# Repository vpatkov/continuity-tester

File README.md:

# Continuity Tester

Ultra low-voltage and fast continuity tester. Digital multimeters are very good
at precise measurements but usually not so good at continuity testing. This
little tester solves the problem.

- **Open terminals voltage is 100 mV, short terminals current is 100 μA.**
  Suitable for in-circuit testing (keep p-n junctions closed) without the
  risk of damaging sensitive components. DMMs usually apply several volts or
  milliamps to the terminals (and not always specified).

- **Resistance-dependent beeper tones with chromatic steps.**
  Allows you to differentiate resistance by ear without moving your viewpoint.
  The range is 0–10 Ω with 1 Ω steps. DMMs usually have a pretty big threshold
  and require you to look at the screen to read the resistance, e.g. if you
  want to catch a bad connection.

- **Detects shorts of 1 ms with an ensured minimal beep duration of 100 ms.**
  Suitable for finding connections by sweeping and brushing without the risk
  of missing a beep. Gold-plated probes are recommended.

- **Auto-hold the minimal resistance.**
  Helps against unstable contacts, e.g. on dirty, oxidized, or lacquered
  boards. The hold resets when the resistance becomes greater than 10 Ω.

- **200 working hours on a single CR2032 cell.**
  Consumes 0.7 mA when on (+0.3 mA when beeping), 0.1 μA when off. After 3
  minutes of inactivity the tester switched off automatically.

- **±30 V input protection.**
  The tester should not be used on a powered circuit, but just in case.
  Also saves against charged capacitors. The input impedance of the tester is
  1 kΩ, so the risk of damaging an accidentally powered circuit under test is
  also low.

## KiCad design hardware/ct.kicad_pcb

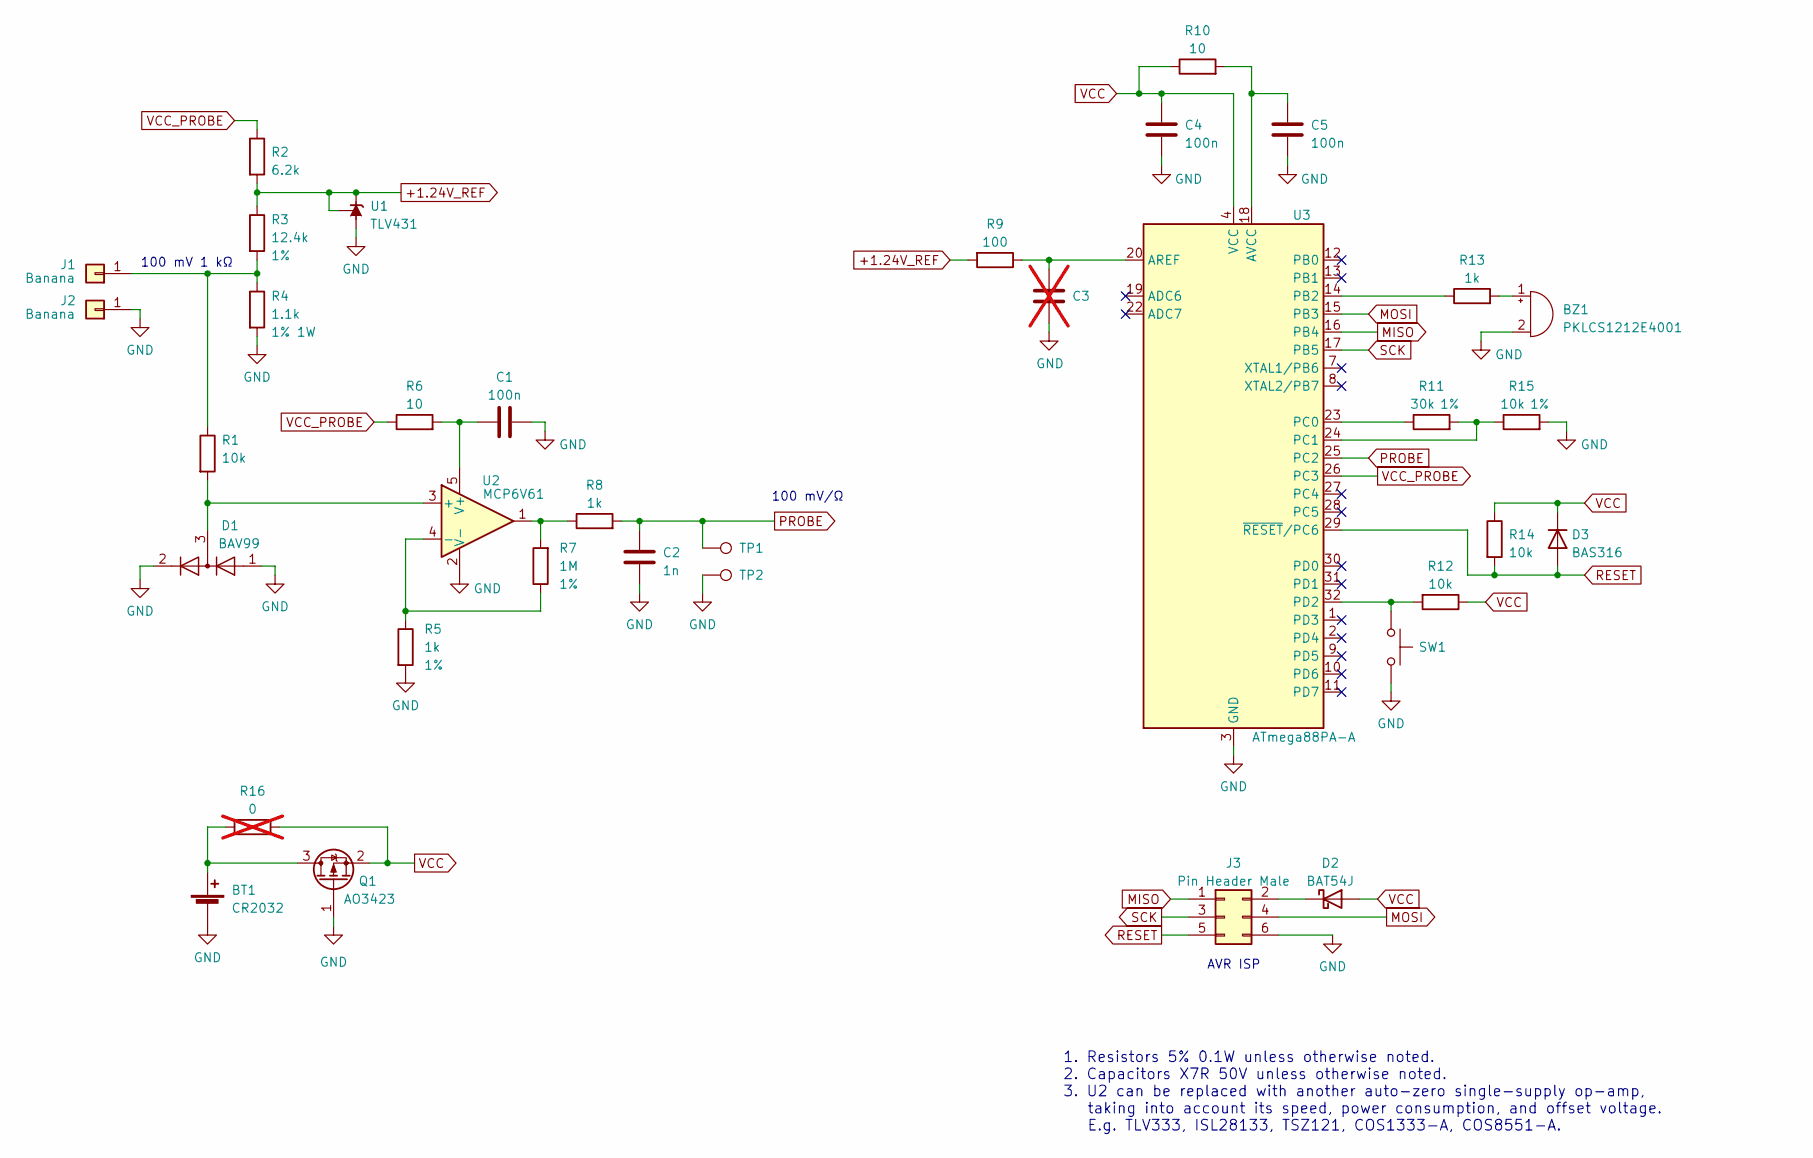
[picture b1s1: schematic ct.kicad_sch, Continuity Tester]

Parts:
BT1: CR2032; BatteryHolder_MPD_BC2003_1x2032
BZ1: PKLCS1212E4001; Buzzer_Murata_PKLCS1212E
C1, C4, C5: 100n; C_0603_1608Metric
C2: 1n; C_0603_1608Metric
C3: C_0603_1608Metric; not fitted
D1: BAV99; SOT-23
D2: BAT54J; D_SOD-323F
D3: BAS316; D_SOD-323
J1, J2: Banana; Banana_Cliff_FCR7350x_S16N-PC_Horizontal
J3: Pin Header Male; PinHeader_2x03_P2.54mm_Vertical
Q1: AO3423; SOT-23
R1, R12, R14, R15: 10k; R_0603_1608Metric
R2: 6.2k; R_0603_1608Metric
R3: 12.4k; R_0603_1608Metric
R4: 1.1k; R_2512_6332Metric
R5, R8, R13: 1k; R_0603_1608Metric
R6, R10: 10; R_0603_1608Metric
R7: 1M; R_0603_1608Metric
R9: 100; R_0603_1608Metric
R11: 30k; R_0603_1608Metric
R16: 0; R_0603_1608Metric; not fitted
SW1: Tactile Button; SW_PUSH_6mm
TP1, TP2: TestPoint; TestPoint_Loop_D3.50mm_Drill0.9mm_Beaded
U1: TLV431; SOT-23
U2: MCP6V61; SOT-23-5
U3: ATmega88PA-A; TQFP-32_7x7mm_P0.8mm

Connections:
+1.24V_REF: R2.2, R3.1, R9.2, U1.1 (K), U1.2 (REF)
GND: BT1.2 (-), BZ1.2 (+), C1.2, C2.2, C3.2, C4.2, C5.2, D1.1 (K), D1.2 (A), J2.1, J3.6, Q1.1 (G), R4.2, R5.2, R15.2, SW1.2, TP2.1, U1.3 (A), U2.2 (V-), U3.3 (GND), U3.5 (GND), U3.21 (GND)
MISO: J3.1, U3.16 (PB4)
MOSI: J3.4, U3.15 (PB3)
unnamed: BT1.1 (+), Q1.3 (D), R16.1
unnamed: BZ1.1 (-), R13.2
unnamed: D2.1 (K), J3.2
unnamed: J1.1, R1.1, R3.2, R4.1
unnamed: R7.2, R8.1, U2.1
unnamed: D1.3 (K), R1.2, U2.3 (+)
unnamed: R5.1, R7.1, U2.4 (-)
unnamed: C1.1, R6.2, U2.5 (V+)
unnamed: C3.1, R9.1, U3.20 (AREF)
unnamed: C5.1, R10.2, U3.18 (AVCC)
unnamed: R13.1, U3.14 (PB2)
unnamed: R11.1, U3.23 (PC0)
unnamed: R11.2, R15.1, U3.24 (PC1)
unnamed: R12.2, SW1.1, U3.32 (PD2)
PROBE: C2.1, R8.2, TP1.1, U3.25 (PC2)
RESET: D3.2 (A), J3.5, R14.2, U3.29 (~RESET/PC6)
SCK: J3.3, U3.17 (PB5)
VCC: C4.1, D2.2 (A), D3.1 (K), Q1.2 (S), R10.1, R12.1, R14.1, R16.2, U3.4 (VCC), U3.6 (VCC)
VCC_PROBE: R2.1, R6.1, U3.26 (PC3)

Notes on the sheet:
100 mV/Ω
AVR ISP
1. Resistors 5% 0.1W unless otherwise noted. 2. Capacitors X7R 50V unless otherwise noted. 3. U2 can be replaced with another auto-zero single-supply op-amp, taking into account its speed, power consumption, and offset voltage. E.g. TLV333, ISL28133, TSZ121, COS1333-A, COS8551-A.
100 mV 1 kΩ

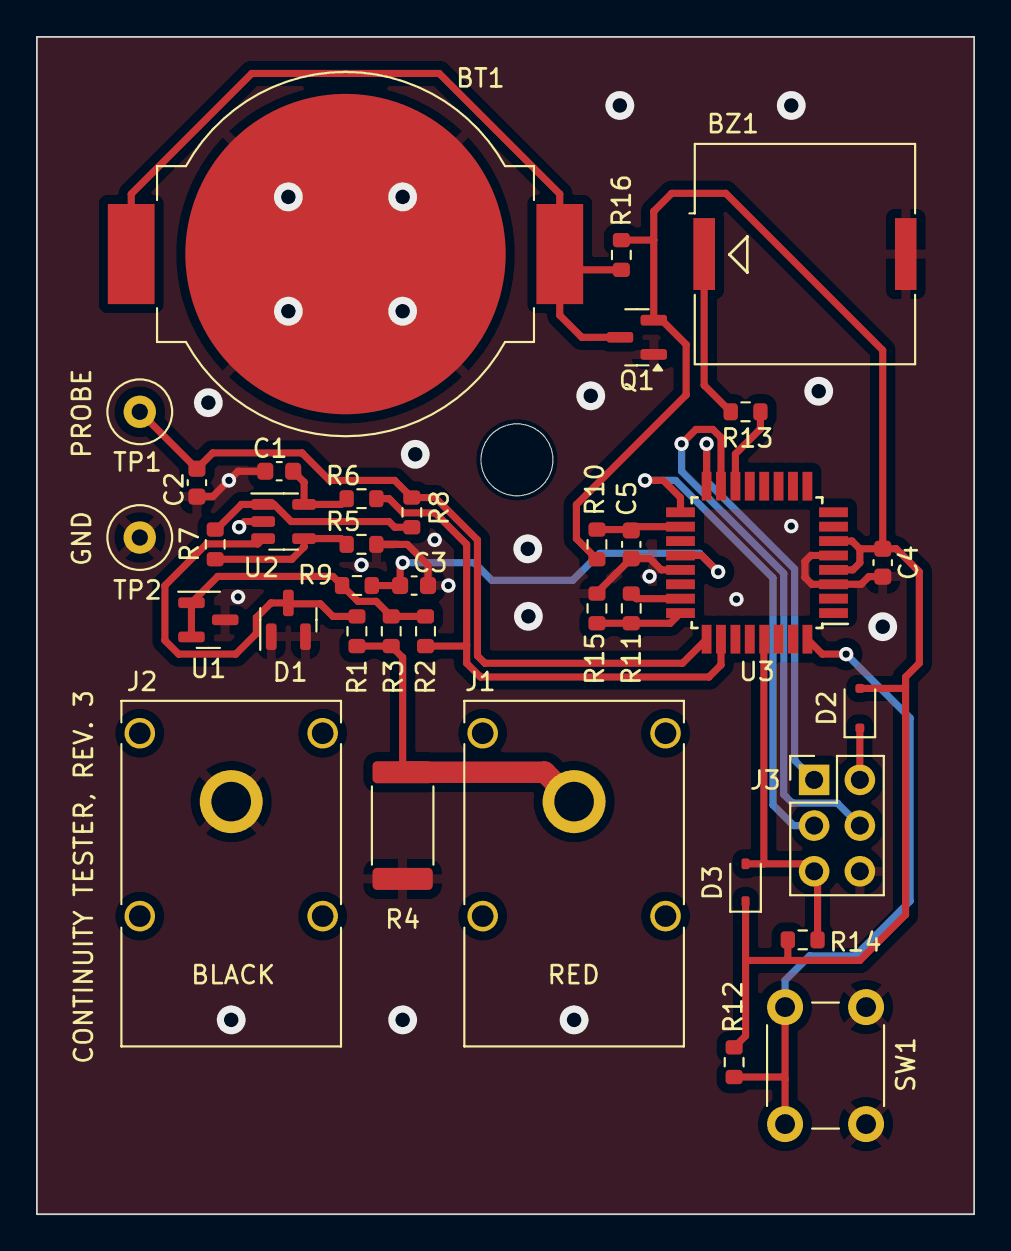
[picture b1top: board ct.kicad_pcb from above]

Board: 2 copper layers, 52.1 x 65.4 mm, 36 parts (0 on the bottom side), 23 nets.

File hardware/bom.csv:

"Reference","Qty","Value","Footprint","Note"
"BT1","1","CR2032","Battery:BatteryHolder_MPD_BC2003_1x2032",""
"BZ1","1","PKLCS1212E4001","Buzzer_Beeper:Buzzer_Murata_PKLCS1212E",""
"C1,C4,C5","3","100n","Capacitor_SMD:C_0603_1608Metric",""
"C2","1","1n","Capacitor_SMD:C_0603_1608Metric",""
"D1","1","BAV99","Package_TO_SOT_SMD:SOT-23",""
"D2","1","BAT54J","Diode_SMD:D_SOD-323F",""
"D3","1","BAS316","Diode_SMD:D_SOD-323",""
"J1,J2","2","Banana","Connector:Banana_Cliff_FCR7350x_S16N-PC_Horizontal",""
"J3","1","Pin Header Male","Connector_PinHeader_2.54mm:PinHeader_2x03_P2.54mm_Vertical",""
"Q1","1","AO3423","Package_TO_SOT_SMD:SOT-23",""
"R1,R12,R14","3","10k","Resistor_SMD:R_0603_1608Metric",""
"R2","1","6.2k","Resistor_SMD:R_0603_1608Metric",""
"R3","1","12.4k","Resistor_SMD:R_0603_1608Metric","1%"
"R4","1","1.1k","Resistor_SMD:R_2512_6332Metric","1% 1W"
"R5","1","1k","Resistor_SMD:R_0603_1608Metric","1%"
"R6,R10","2","10","Resistor_SMD:R_0603_1608Metric",""
"R7","1","1M","Resistor_SMD:R_0603_1608Metric","1%"
"R8,R13","2","1k","Resistor_SMD:R_0603_1608Metric",""
"R9","1","100","Resistor_SMD:R_0603_1608Metric",""
"R11","1","30k","Resistor_SMD:R_0603_1608Metric","1%"
"R15","1","10k","Resistor_SMD:R_0603_1608Metric","1%"
"SW1","1","Tactile Button","Button_Switch_THT:SW_PUSH_6mm","Height 15mm"
"TP1,TP2","2","TestPoint","TestPoint:TestPoint_Loop_D3.50mm_Drill0.9mm_Beaded",""
"U1","1","TLV431","Package_TO_SOT_SMD:SOT-23",""
"U2","1","MCP6V61","Package_TO_SOT_SMD:SOT-23-5",""
"U3","1","ATmega88PA-A","Package_QFP:TQFP-32_7x7mm_P0.8mm",""

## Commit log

2023-07-02 Add alternatives for U2
2023-07-04 Add a case sticker
2023-07-08 Minor case improvement
2023-08-07 Change U2 to MCP6V61
2024-12-22 Fix typo
2025-08-31 Add reverse polarity protection for battery
2025-08-31 Add bypass to the reverse polarity protection
2025-09-01 Fix typos and grammar in README

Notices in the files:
README.md:
CC0 button
